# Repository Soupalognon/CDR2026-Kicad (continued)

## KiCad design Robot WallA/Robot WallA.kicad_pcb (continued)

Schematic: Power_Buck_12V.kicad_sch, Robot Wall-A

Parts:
C83, C85, C93, C117: 4.7uF/50V; C_1210_3225Metric_Pad1.33x2.70mm_HandSolder; Manufacturer_Part_Number GRM32ER71H475KA88L
C84: 330uF; CAPPRD500W65D1000H1800; Manufacturer_Part_Number EEU-FC1V331
C88: 10nF/50V; C_0805_2012Metric_Pad1.18x1.45mm_HandSolder; Manufacturer_Part_Number CL21B103KBANNNC
C89, C91, C92: 47nF/50V; C_0603_1608Metric_Pad1.08x0.95mm_HandSolder; Manufacturer_Part_Number CC0603KPX7R9BB473
C90: 2.2uF/50V; C_1210_3225Metric_Pad1.33x2.70mm_HandSolder; Manufacturer_Part_Number C3225X7R1H225K250AB
D7: LED_RED; LED_0603_1608Metric; Manufacturer_Part_Number LS L29K-G1J2-1
Q3: BSS138; SOT-23; Manufacturer_Part_Number BSS138
R39: 5.1k; R_0603_1608Metric_Pad0.98x0.95mm_HandSolder; Manufacturer_Part_Number CRCW06035K10FKEA
R41: 10k; R_0603_1608Metric_Pad0.98x0.95mm_HandSolder; Manufacturer_Part_Number 667-ERJ-3GEYJ103V; not fitted
R53: 549R; R_0603_1608Metric_Pad0.98x0.95mm_HandSolder; Manufacturer_Part_Number RC0603FR-07549RL
RV4: Trim 2k; TC42X2202E; Manufacturer_Part_Number TC42X-2-202E
U8: PTN78020W; Texas_EUK_R-PDSS-T7_THT; Manufacturer_Part_Number PTN78020WAD

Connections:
/Power/12V: C83.1, C84.1, C85.1, C88.1, D7.2 (A), U8.5 (VO_Sense), U8.6 (VO); also elsewhere on the board
/Power/GPIO_ENABLE_POWER_SUPPLIES: Q3.1 (G), R41.1; also elsewhere on the board
/Power/Power_Buck_12V/IN: C89.1, C90.1, C91.1, C92.1, C93.1, C117.1, U8.2 (VI); also elsewhere on the board
/Power/Power_Buck_12V/TRIM: R53.1, U8.4 (VO_Adj)
GND: C83.2, C84.2, C85.2, C88.2, C89.2, C90.2, C91.2, C92.2, C93.2, C117.2, Q3.2 (S), R39.2, R41.2, RV4.2, U8.1 (GND), U8.7 (GND); also elsewhere on the board
unnamed: D7.1 (K), R39.1
unnamed: Q3.3 (D), U8.3 (~Inhibit)
unnamed: R53.2, RV4.1

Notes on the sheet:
Si Vin=16V et Vout 5V --> Rendement >93% Avec un courant de 3A théorique (PC calcul) --> Puissance à dissiper de 1,05W Ne doit pas dépasser 55°C D'après la doc il ne faut pas forcément de radiateur, juste un ventilo Mettre un capteur de température pour monitorer?

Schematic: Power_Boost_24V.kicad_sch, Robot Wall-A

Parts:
C62, C69: 470uF/50V; CAPAE1700X1700N; Manufacturer_Part_Number EMVE500ARA471MLH0S
C63, C64, C65, C66, C67: 4.7uF/50V; C_0805_2012Metric_Pad1.18x1.45mm_HandSolder; Manufacturer_Part_Number GRM21BR61H475ME51L
C68: 10nF/50V; C_0805_2012Metric_Pad1.18x1.45mm_HandSolder; Manufacturer_Part_Number CL21B103KBANNNC
C70, C71, C72, C73, C74, C75, C76: 47nF/50V; C_0603_1608Metric_Pad1.08x0.95mm_HandSolder; Manufacturer_Part_Number CC0603KPX7R9BB473
C77, C78, C79, C80, C81: 4.7uF/50V; C_1210_3225Metric_Pad1.33x2.70mm_HandSolder; Manufacturer_Part_Number GRM32ER71H475KA88L
C82: 470pF; C_0603_1608Metric_Pad1.08x0.95mm_HandSolder; Manufacturer_Part_Number C0603C471K5RACTU
D6: LED_RED; LED_0603_1608Metric; Manufacturer_Part_Number LS L29K-G1J2-1
H7: ThermalPad; Manufacturer_Part_Number 404035125
H8: Heatsink; 374524B60023G; Manufacturer_Part_Number 374524B60023G
IC7: ABXS005A4X341-SRZ; ABXS005A4X341SRZ; Manufacturer_Part_Number ABXS005A4X341-SRZ
JP18: Closed; SolderJumper-2_P1.3mm_Bridged_RoundedPad1.0x1.5mm
JP19: Open; SolderJumper-2_P1.3mm_Open_RoundedPad1.0x1.5mm
Q2: BSS138; SOT-23; Manufacturer_Part_Number BSS138
R33: 11.3k; R_0603_1608Metric_Pad0.98x0.95mm_HandSolder; Manufacturer_Part_Number CRCW060311K3FKEA
R34: 200k; R_0603_1608Metric_Pad0.98x0.95mm_HandSolder; Manufacturer_Part_Number CRCW0603200KFKEC
R35: 100k; R_0603_1608Metric_Pad0.98x0.95mm_HandSolder; Manufacturer_Part_Number RCA0603100KFKEAHP
R36: 10k; R_0603_1608Metric_Pad0.98x0.95mm_HandSolder; Manufacturer_Part_Number 667-ERJ-3GEYJ103V; not fitted
R37: 10,553k/0.5%; R_0603_1608Metric_Pad0.98x0.95mm_HandSolder; Manufacturer_Part_Number RC0603DR-0710K5L
R38: 10k; R_0603_1608Metric_Pad0.98x0.95mm_HandSolder; Manufacturer_Part_Number 667-ERJ-3GEYJ103V
RV1: Trim 2k; TC42X2202E; Manufacturer_Part_Number TC42X-2-202E; not fitted
U2, U3: 125700D00000G; Manufacturer_Part_Number 125700D00000G

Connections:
/MCU/3V3: R36.2; also elsewhere on the board
/Power/24V: C62.1, C63.1, C64.1, C65.1, C66.1, C67.1, C68.1, D6.2 (A), IC7.2 (VOUT); also elsewhere on the board
/Power/GPIO_ENABLE_POWER_SUPPLIES: Q2.1 (G), R38.1; also elsewhere on the board
/Power/GPIO_PGOOD: IC7.13 (PGOOD), R36.1; also elsewhere on the board
/Power/Power_Boost_24V/ENABLE: IC7.12 (ENABLE), Q2.3 (D), R35.2
/Power/Power_Boost_24V/IN: C69.1, C70.1, C71.1, C72.1, C73.1, C74.1, C75.1, C76.1, C77.1, C78.1, C79.1, C80.1, C81.1, IC7.3 (VIN_1), IC7.5 (VIN_2), R35.1; also elsewhere on the board
/Power/Power_Boost_24V/SENSE+: IC7.10 (SENSE+), R34.2
/Power/Power_Boost_24V/TRIM: C82.1, IC7.11 (TRIM), R37.2
GND: C62.2, C63.2, C64.2, C65.2, C66.2, C67.2, C68.2, C69.2, C70.2, C71.2, C72.2, C73.2, C74.2, C75.2, C76.2, C77.2, C78.2, C79.2, C80.2, C81.2, IC7.1 (PGND_1), IC7.4 (PGND_2), IC7.6 (PGND_3), IC7.7 (SGND), JP18.1 (A), Q2.2 (S), R33.2, R38.2, RV1.2, U2.1, U2.2, U3.1, U3.2; also elsewhere on the board
unnamed: C82.2, R34.1
unnamed: D6.1 (K), R33.1
unnamed: JP18.2 (B), JP19.1 (A), R37.1
unnamed: JP19.2 (B), RV1.1

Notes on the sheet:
footprint size 10n --> 0805 47n --> 0603 4,7uF --> 1210
Anchors for heat sink Footprint placement : https://www.mouser.fr/datasheet/2/2/Aavid_01112021_Board_Level_Cooling_3745-1953702.pdf
Fan required minimum 3,5CFM
Si Vin=16V et Vout 24V --> Rendement >95% Avec un courant de 5A théorique --> Puissance à dissiper de 6W On ne compte pas les dT(°C/W) des gap filters car faibles (à vérifier!) Q1 ne doit pas dépasser 135°C (marge à 90°C pour sécurité) Si T ambiant de 30°C alors dT(°C/W) radiateur de (90-30)/6 = 10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

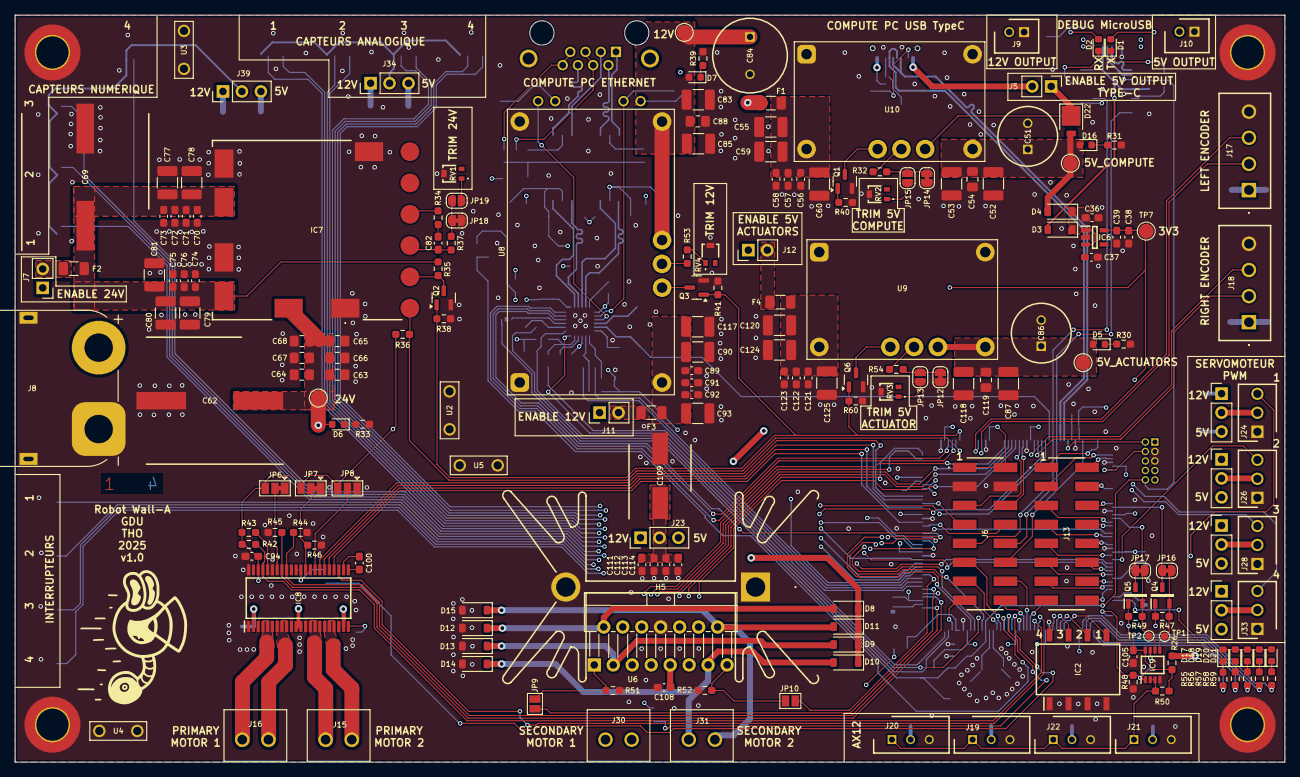
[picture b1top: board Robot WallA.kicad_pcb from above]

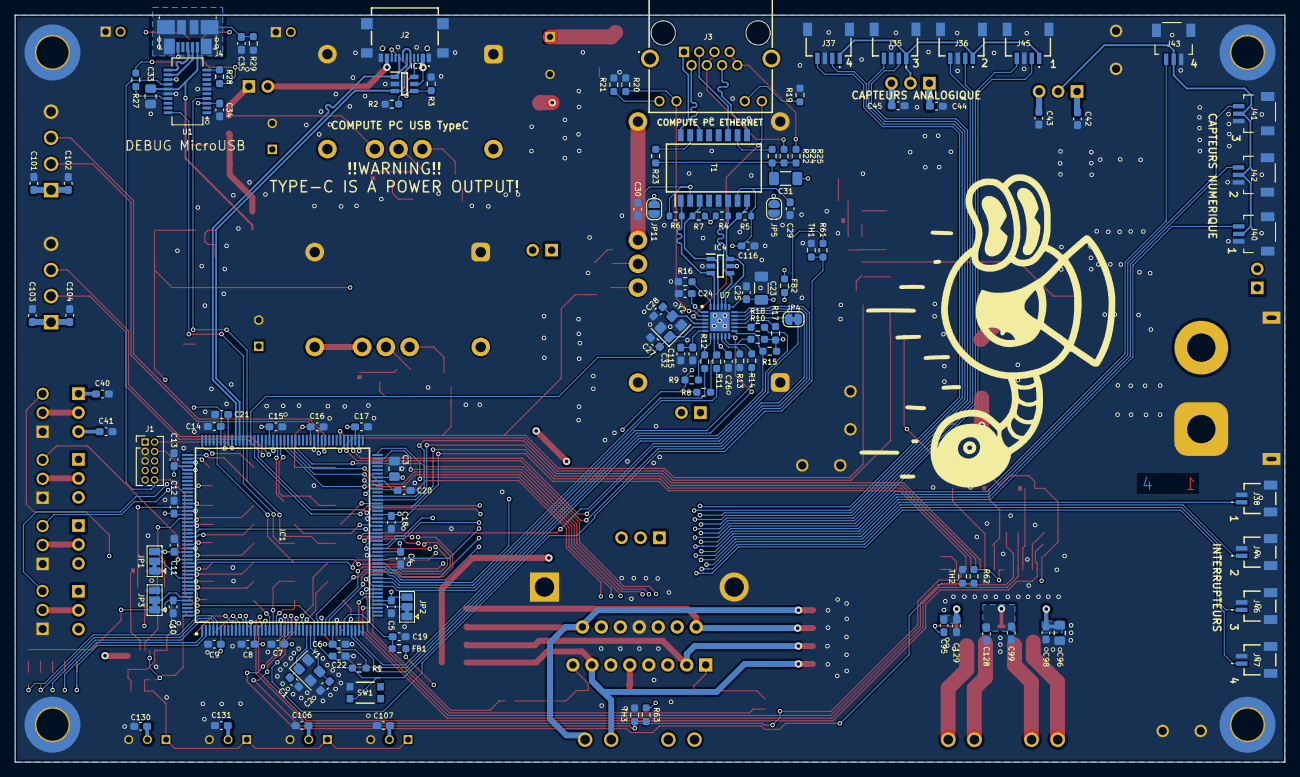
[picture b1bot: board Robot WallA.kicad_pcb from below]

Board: 4 copper layers, 170.0 x 100.0 mm, 328 parts (125 on the bottom side), 219 nets.

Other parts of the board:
Q1: BSS138; SOT-23
R40: 10k; R_0603_1608Metric_Pad0.98x0.95mm_HandSolder

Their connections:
/Power/Power_Buck_5V_Compute/GPIO_ENABLE: Q1.1 (G), R40.1
GND: Q1.2 (S), R40.2; also elsewhere on the board
unnamed 205: Q1.3 (D); also elsewhere on the board

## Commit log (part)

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2025-08-05 ADD: go go
2025-08-05 ADD: GPIO
2025-08-05 ADD: Ethernet
2025-08-05 filled mototr driver schematic
2025-08-05 comment
2025-08-23 List of Modifs:
    Corrected power supply sheet
    Updated motor driver sheet
    Added a project name to a lot of sheets (don't know why...)
2025-08-23 ADD supplies to UC
2025-08-25 Updated MCU sheet
    Added decoupling capacitors
    Linked Ethernet to MCU
    Started Usb linking to MCU
2025-08-30 Updated a lot of stuff:
    Added encoders,
    Added 5V power supply for actuators
    Added 12V power supply for actuators
    Renamed sheets to be clearer
    Added usb debug
    Modify MCU sheet to be A3 format
2025-08-30 Renamed folder to be clearer (From PCB to Robot WallA)
2025-08-30 Continued to link MCU pins, Added a sheet for servomotors and optional 2 DC motors.
2025-08-31 Defined every footprints
2025-09-01 Created sensors sheet (for distance meters and others)
2025-09-01 Startes to write README
2025-09-01 Updated README and add jumper part reference
2025-09-02 Updated USB UART converter, Linked telemeter sensors.
    Updated components indicators
2025-09-06 Added standard switchs, debug leds and 12V and 5V connectors
2025-09-08 Begin to route ethenet, usb, 24V power supply.
    Reworked Ethernet sheet because it was too hard to read
2025-09-08 Continue to route
2025-09-12 continue
2025-09-13 Reworked 12V and 5V power supplies, continue routing
2025-09-15 Conitnue routing
2025-09-20 Correct a lot of error in DRC
2025-09-20 Corrected all DRC erros, added info on PCB
    modified distance meter connectors to be horizontal
2025-09-20 Updated fab files.
2025-09-20 Moved 24V boost to be correct assembly issue with heatsink fixation collisions
2025-09-21 Added diode for Type-C connector in case we accidentally power the board with this connector.
    Updated fab files
2025-09-21 Added to BOM connectors and socket
    Updated fab files
2025-09-21 Modified a bit pin header pins to allow I2C,SPI and CAN
2025-09-21 Updated Fab files
2025-09-21 Added pin header for 5V USB type output, to be able to disable it
    Updated fab files
2025-09-23 Added 3 thermistor to measure temperature near 12V and 24V power supplies and near motor drivers
2025-09-23 Modified footprint to simplify BOM. Finalized BOM.
    Updated fab files
2025-09-23 Added Thermal pads for heatsinks in BOM.
    Updated fab files
2025-10-08 Added a trim to 24V in case of (defaulty unplaced)
    Updated fab files
2025-10-10 Finalized BOM
2025-10-15 Added logo
    Replaced out of stock components
2025-10-15 Moved Debug LEDs to be on top layer.
    Updated fab files
2025-10-24 Added pictures
2026-05-09 Corrected schematic labels encoders according to PCB labels... (inversion...)
    Add fab files
    cleaned
2026-05-09 updated schematic pdf
